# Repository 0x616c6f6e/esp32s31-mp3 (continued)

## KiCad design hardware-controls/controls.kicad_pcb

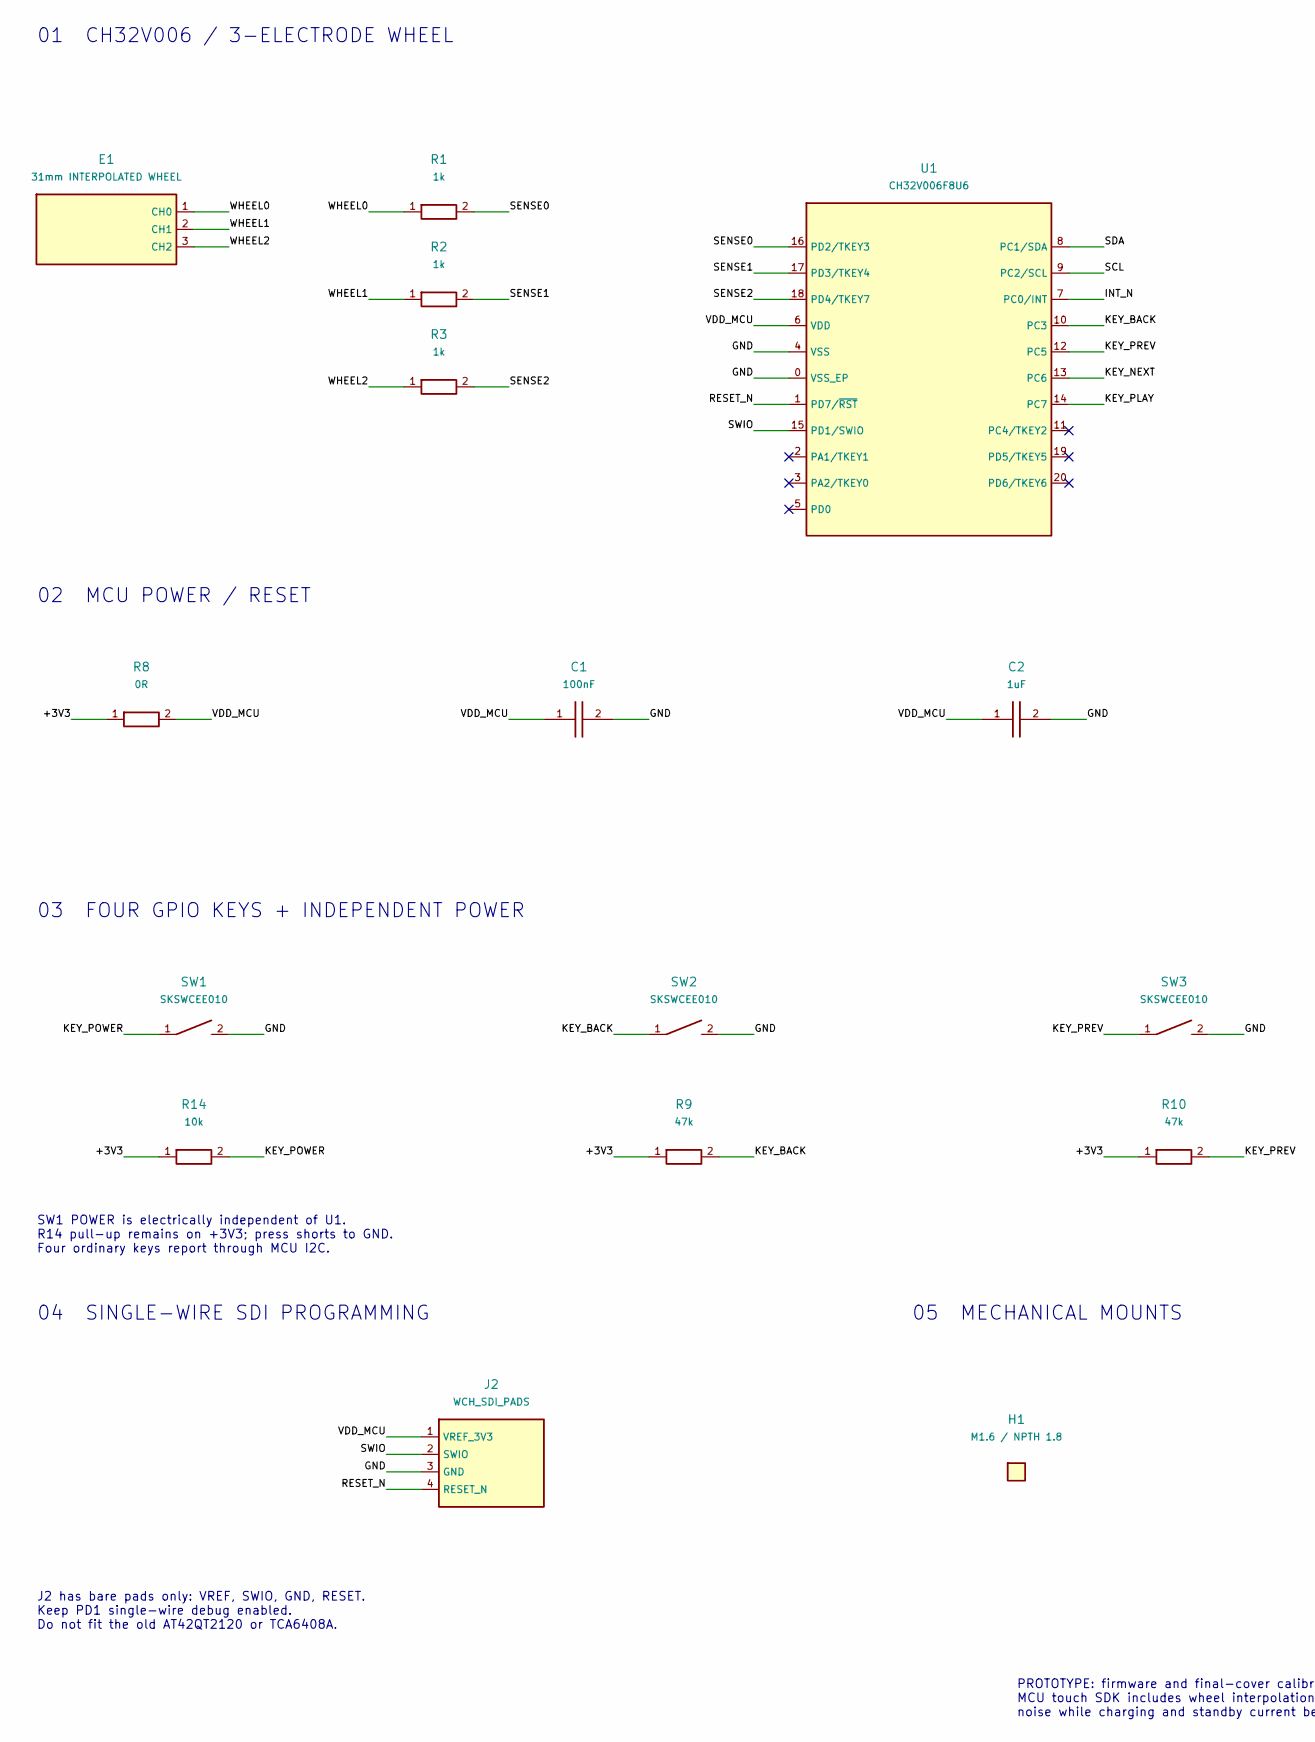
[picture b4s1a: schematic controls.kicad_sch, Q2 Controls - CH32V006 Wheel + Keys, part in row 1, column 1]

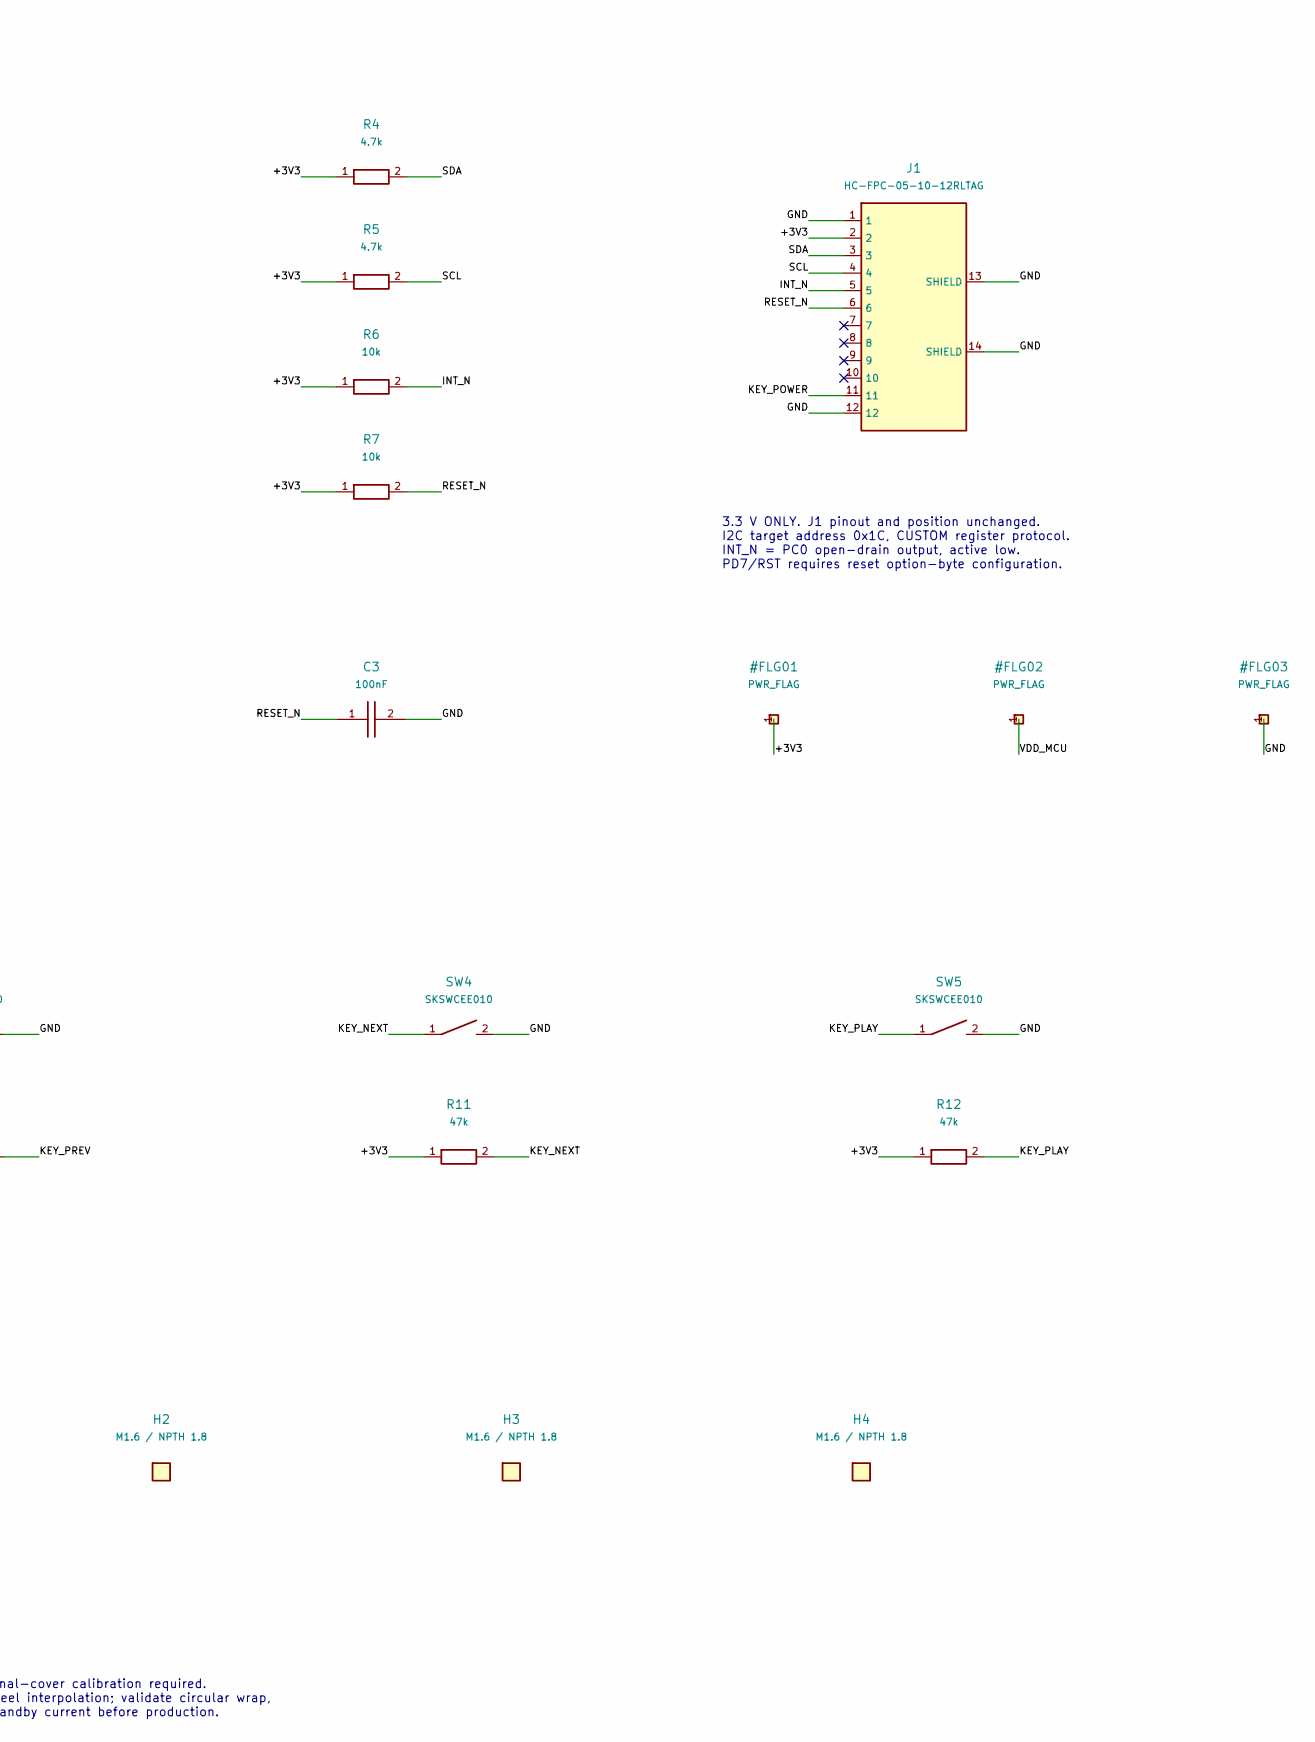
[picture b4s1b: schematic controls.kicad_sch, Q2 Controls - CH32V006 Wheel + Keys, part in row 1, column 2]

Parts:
C1, C3: 100nF; C0402
C2: 1uF; C0402
E1: 31mm INTERPOLATED WHEEL; Wheel_D31
H1, H2, H3, H4: M1.6 / NPTH 1.8; Mount_1.8
J1: HC-FPC-05-10-12RLTAG; HCTL_FPC12
J2: WCH_SDI_PADS; SDI_4_Pads
R1, R2, R3: 1k; R0402
R4, R5: 4.7k; R0402
R6, R7, R14: 10k; R0402
R8: 0R; R0402
R9, R10, R11, R12: 47k; R0402
SW1, SW2, SW3, SW4, SW5: SKSWCEE010; SKSW_3x2
U1: CH32V006F8U6; CH32V006_QFN20

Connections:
/+3V3: J1.2, R4.1, R5.1, R6.1, R7.1, R8.1, R9.1, R10.1, R11.1, R12.1, R14.1
/GND: C1.2, C2.2, C3.2, J1.1, J1.12, J1.13 (SHIELD), J1.14 (SHIELD), J2.3 (GND), SW1.2, SW2.2, SW3.2, SW4.2, SW5.2, U1.0 (VSS_EP), U1.4 (VSS)
/INT_N: J1.5, R6.2, U1.7 (PC0/INT)
/KEY_BACK: R9.2, SW2.1, U1.10 (PC3)
/KEY_NEXT: R11.2, SW4.1, U1.13 (PC6)
/KEY_PLAY: R12.2, SW5.1, U1.14 (PC7)
/KEY_POWER: J1.11, R14.2, SW1.1
/KEY_PREV: R10.2, SW3.1, U1.12 (PC5)
/RESET_N: C3.1, J1.6, J2.4 (RESET_N), R7.2, U1.1 (PD7/~RST)
/SCL: J1.4, R5.2, U1.9 (PC2/SCL)
/SDA: J1.3, R4.2, U1.8 (PC1/SDA)
/SENSE0: R1.2, U1.16 (PD2/TKEY3)
/SENSE1: R2.2, U1.17 (PD3/TKEY4)
/SENSE2: R3.2, U1.18 (PD4/TKEY7)
/SWIO: J2.2 (SWIO), U1.15 (PD1/SWIO)
/VDD_MCU: C1.1, C2.1, J2.1 (VREF_3V3), R8.2, U1.6 (VDD)
/WHEEL0: E1.1 (CH0), R1.1
/WHEEL1: E1.2 (CH1), R2.1
/WHEEL2: E1.3 (CH2), R3.1

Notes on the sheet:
01 CH32V006 / 3-ELECTRODE WHEEL
02 MCU POWER / RESET
03 FOUR GPIO KEYS + INDEPENDENT POWER
04 SINGLE-WIRE SDI PROGRAMMING
05 MECHANICAL MOUNTS
3.3 V ONLY. J1 pinout and position unchanged. I2C target address 0x1C, CUSTOM register protocol. INT_N = PC0 open-drain output, active low. PD7/RST requires reset option-byte configuration.
SW1 POWER is electrically independent of U1. R14 pull-up remains on +3V3; press shorts to GND. Four ordinary keys report through MCU I2C.
J2 has bare pads only: VREF, SWIO, GND, RESET. Keep PD1 single-wire debug enabled. Do not fit the old AT42QT2120 or TCA6408A.
PROTOTYPE: firmware and final-cover calibration required. MCU touch SDK includes wheel interpolation; validate circular wrap, noise while charging and standby current before production.

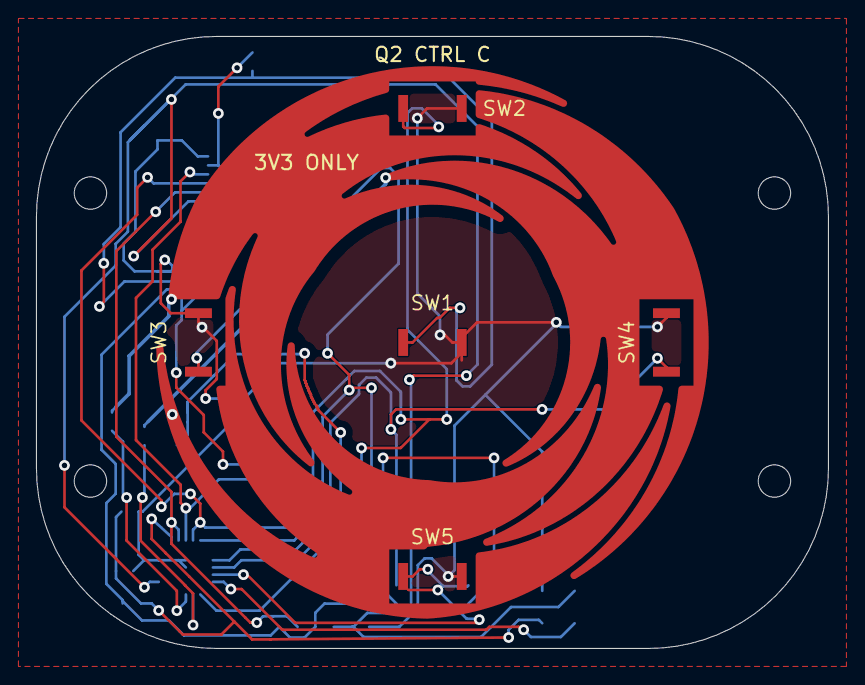
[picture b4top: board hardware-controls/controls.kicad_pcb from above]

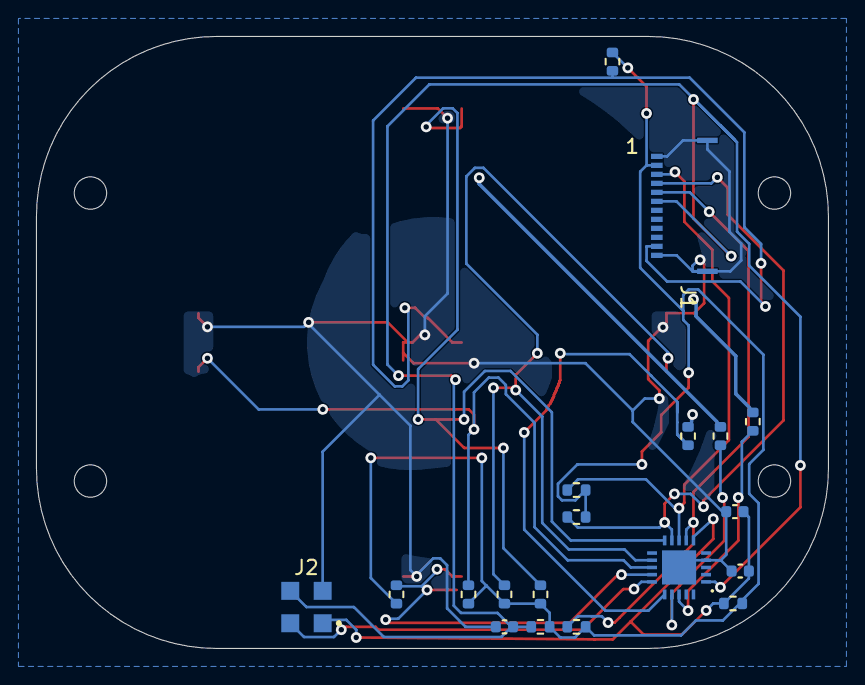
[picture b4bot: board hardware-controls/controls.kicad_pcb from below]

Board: 2 copper layers, 44.0 x 34.0 mm, 29 parts (19 on the bottom side), 19 nets.

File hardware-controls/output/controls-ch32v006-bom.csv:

"Designator","Value","Footprint","Quantity"
"C1,C3","100nF","Controls:C0402","2"
"C2","1uF","Controls:C0402","1"
"J1","HC-FPC-05-10-12RLTAG","Controls:HCTL_FPC12","1"
"R1-R3","1k","Controls:R0402","3"
"R4,R5","4.7k","Controls:R0402","2"
"R6,R7,R14","10k","Controls:R0402","3"
"R8","0R","Controls:R0402","1"
"R9-R12","47k","Controls:R0402","4"
"SW1-SW5","SKSWCEE010","Controls:SKSW_3x2","5"
"U1","CH32V006F8U6","Controls:CH32V006_QFN20","1"

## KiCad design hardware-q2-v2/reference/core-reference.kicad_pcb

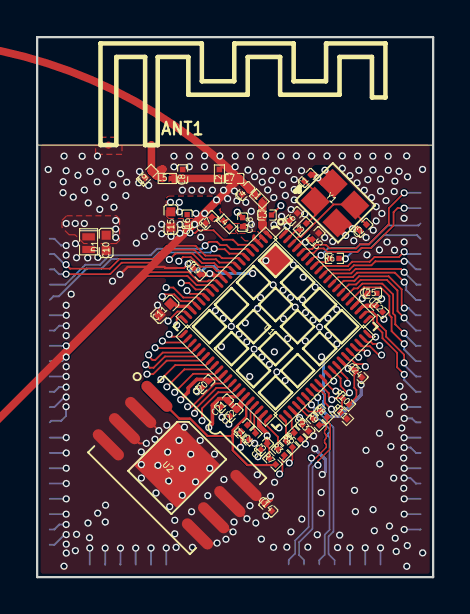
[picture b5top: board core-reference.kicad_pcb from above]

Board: 4 copper layers, 22.0 x 30.0 mm, 47 parts (1 on the bottom side), 85 nets.

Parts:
ANT1: ESP-ANT-2G-MIFA-G2-L15P8W5P6-V1P1
C1, C2, C3, C4, C5, C6, C7, C8, C12, C13, C14, C16, C17, C18, C19, C20, C21, C22, C23, C24, C25: C0201
C9: DFN0603_A
C10, C11, C15: C0402
D1: SOD882
L1, L2, L3, L4, L5: L0201
R1, R2, R3, R4, R5, R6, R7, R8, R9, R10, R11: R0201
U1: QFN80_0P35_8_E6P5_A
U2: WSON8_1P27_8X6_E4P3X3P4
U3: QFN94_0P85_22P6X20P6_MINI
Y1: XTAL3225_2016

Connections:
ANT: C3.1, L1.2, U1.1
EN: U1.4, U3.5
GND: ANT1.2, C1.2, C2.2, C3.2, C4.2, C5.2, C6.2, C8.2, C9.2, C10.2, C11.2, C12.2, C13.2, C14.2, C15.2, C16.2, C17.2, C18.2, C19.2, C20.2, C21.2, C22.2, C23.2, C24.2, C25.2, D1.1, L2.2, R11.2, U1.81, U2.4, U2.9, U3.1, U3.2, U3.26, U3.47, U3.48, U3.72, U3.73, U3.74, U3.75, U3.76, U3.77, U3.78, U3.79, U3.80, U3.81, U3.82, U3.83, U3.84, U3.85, U3.86, U3.87, U3.88, U3.89, U3.90, U3.92, U3.93, U3.94, U3.95, U3.96, U3.97, U3.98, U3.99, Y1.2, Y1.4
IO0: U1.5, U3.8
IO1: U1.6, U3.9
IO2: U1.7, U3.6
IO3: U1.8, U3.7
IO4: U1.9, U3.10
IO5: U1.10, U3.11
IO6: U1.12, U3.12
IO7: U1.13, U3.13
IO8: U1.14, U3.14
IO9: U1.15, U3.15
IO10: U1.16, U3.16
IO11: U1.17, U3.17
IO12: U1.19, U3.18
IO13: U1.20, U3.19
IO14: U1.21, U3.20
IO15: U1.22, U3.21
IO16: U1.23, U3.22
IO17: U1.24, U3.23
IO18: U1.25, U3.24
IO19: U1.26, U3.25
IO33: U1.46, U3.42
IO34: U1.47, U3.43
IO35: U1.48, U3.44
IO36: R10.1, R11.1, U1.49, U3.45
IO37: U1.50, U3.46
IO38: U1.51, U3.49
IO39: U1.52, U3.50
IO40: U1.53, U3.51
IO42: U1.55, U3.52
IO43: U1.56, U3.53
IO44: U1.57, U3.54
IO45: U1.58, U3.55
IO46: U1.59, U3.56
IO47: U1.60, U3.57
IO48: U1.61, U3.58
IO49: U1.62, U3.59
IO50: U1.65, U3.60
IO51: U1.66, U3.61
IO52: U1.67, U3.62
IO53: U1.68, U3.63
IO54: U1.69, U3.64
IO55: U1.70, U3.65
IO56: U1.71, U3.66
IO57: U1.72, U3.67
IO60: U1.75, U3.70
IO61: U1.76, U3.71
N20805107: C18.1, L4.2, U1.2, U1.3
N20805446: R6.1, U1.73
N20805524: L3.1, U1.79
N20805709: R4.1, U1.41
N20805715: R5.1, U1.42
N20805727: R3.1, U1.40
N20805734: R2.1, U1.38
N20805749: R1.1, U1.37
N20805764: R8.1, U1.45
N20805766: R9.1, U1.44
RF: C4.1, C7.2, L1.1
RF1: C7.1, C8.1, L2.1, L5.2
RF_ANT: ANT1.1, C9.1, L5.1
RX0: U1.74, U3.69
SD_CLK: U1.32, U3.31
SD_CMD: U1.33, U3.32
SD_D0: U1.27, U3.27
SD_D1: U1.28, U3.28
SD_D2: U1.29, U3.29
SD_D3: U1.31, U3.30
SPICLK: R4.2, U2.6
SPICS: R7.2, U1.36, U2.1
SPID: R5.2, U2.5
SPIHD: R3.2, U2.7
SPIQ: R1.2, U2.2
SPIWP: R2.2, U2.3
TX0: R6.2, U3.68
USB_DM: R8.2, U3.41
USB_DP: R9.2, U3.40
VDD33: C5.1, C6.1, C10.1, C15.1, C16.1, C17.1, C19.1, C23.1, C24.1, C25.1, D1.2, L4.1, R10.2, U1.11, U1.43, U1.54, U1.64, U1.77, U1.80, U3.3, U3.4
VDD_LDO_1P8: C20.1, C21.1, C22.1, U1.30, U1.34, U1.35
VDD_SPI: C13.1, C14.1, R7.1, U1.39, U2.8
VREF_ADC: C12.1, U1.63
VREF_TOUCH: C11.1, U1.18
XTAL_N: C2.1, U1.78, Y1.3
XTAL_P: C1.1, L3.2, Y1.1

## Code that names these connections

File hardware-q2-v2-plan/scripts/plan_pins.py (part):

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def fixed(pin,group,signal,target,reset,notes=''):
 r=rows[pin];assert r['group']=='未分配';r.update(group=group,signal=signal,target=target,reset_requirement=reset,notes=notes,direction='专用')

# LP GPIOs remain available for wake inputs; GPIO0 here is not an ESP32-S31 boot strap.
for g,s,old,target in [(0,'KEY_POWER_SENSE_N','ESP_IO42','FPC1.11 / U6.1，经3.3V隔离检测'),(1,'CTRL_INT_N','ESP_IO43','FPC1.5'),(2,'RTC_INT_N','ESP_IO34','U1.6'),(3,'IMU_INT1','ESP_IO1','U15.4'),(4,'BAT_ALERT_N','ESP_IO35','U14.1'),(5,'CHG_INT_N','BQ25895_INT','U3.7')]:
 assign(g,'唤醒/中断',s,old,'输入',target,'输入；上拉仅接3.3V；GPIO3极性由IMU配置','LP GPIO；唤醒需要固件配置。KEY必须隔离GEK供电域；不得原样直连。' if g==0 else 'LP GPIO；可按需要配置唤醒，保持供电时才有效。')
assign(6,'系统LP I2C','SYS_I2C_SCL','BQ25895_I2C_CLK','开漏双向','U3.5 U14.3 U1.2 U11.2 FPC1.4','外部上拉3.3V','LP I2C，F2；100kHz起步；不是I2C_NUM_2')
assign(7,'系统LP I2C','SYS_I2C_SDA','BQ25895_I2C_SDA','开漏双向','U3.6 U14.2 U1.3 U11.3 FPC1.3','外部上拉3.3V','LP I2C，F2；LP核访问须与主核通过命令/共享内存协调')
for g,s,old,di,t,reset,note in [
 (9,'POWER_OFF_REQ','GEK100_RST','输出','U6.3，经断电防反灌电路','外部下拉；上电低','新增软件关机请求；高有效，需保证掉电后复位脉冲时长'),
 (10,'CTRL_RESET_N','ESP_IO44','开漏输出','FPC1.6','释放，由小板RC上拉','CH32V006 PD7配置硬件复位后才生效'),
 (11,'USB_PATH_SEL','ESP_IO33','输出','U17.2','外部电阻固定默认路径','避开GPIO33复位USB功能；0/1对应哪路须核对U17真值表'),
 (12,'MOTOR_EN','ESP_IO40','输出','U11.5','外部下拉；默认关闭','保留现有R44下拉；PWM/触发使用需按马达驱动配置'),
 (13,'CHG_OTG_EN','BQ25895_OTG_EN','输出','U3.8','外部下拉；默认关闭','保留R12下拉；不得上电即打开OTG'),
 (19,'SD_CARD_DETECT_N','ESP_IO19','输入','CARD2.CD','新增/核对3.3V上拉','检测触点极性以实物卡座导通确认')]:
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 assign(g,'SDMMC',s,old,'输出' if g==24 else '双向',t,'CMD/D0-D3上拉3.3V；CLK不随意加上拉','原生SDIO F0；本板卡接口先用3.3V，不直接改1.8V模式')
for g,s,old,t in [(26,'FLASH_CS_N','ESP_FLASH_CS','U10.1'),(27,'FLASH_D1','ESP_FLASH_DO','U10.2'),(28,'FLASH_D2','ESP_FLASH_WP','U10.3'),(30,'FLASH_D3','ESP_FLASH_HOLD','U10.7'),(31,'FLASH_CLK','ESP_FLASH_CLK','U10.6'),(32,'FLASH_D0','ESP_FLASH_DI','U10.5')]:
 assign(g,'启动Flash',s,old,'输出' if g in [26,31] else '双向',t,'按启动Flash参考电路','固定MSPI引脚；不分给应用GPIO；U10容量待选，建议与原模组16MB目标一致')
fixed(44,'USB HS','USB_HS_DP','U17.7','专用差分','旧网ESP_USB_DP；不是GPIO44')
fixed(45,'USB HS','USB_HS_DM','U17.6','专用差分','旧网ESP_USB_DN；不是GPIO45')
assign(33,'调试预留','USB_DEBUG_DM','','专用差分','新增调试焊盘/连接器','保留USB Serial/JTAG功能','不再接USB切换SEL；与HS USB不是同一对线，不可并接')
assign(34,'调试预留','USB_DEBUG_DP','','专用差分','新增调试焊盘/连接器','保留USB Serial/JTAG功能','不再接RTC中断；量产无调试连接器时可不装引出件')
for g,s,old,t in [(35,'DAC_I2S_DOUT','DAC_I2S_SDIN','U8.2'),(38,'DAC_I2S_LRCK','DAC_I2S_LRCK','U8.5'),(39,'DAC_RESET_N','DAC_RST#','U8.12'),(40,'DAC_I2S_BCLK','DAC_I2S_SCLK','U8.9')]:
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assign(59,'下载UART0','UART0_RX','CH343P_UART_TX','输入','U12.4 TXD','UART0输入','ESP RX接CH343 TX')
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 assign(g,'启动配置',s,old,'启动采样','启动上拉/下载电路',reset,note)
fixed(4,'复位','CHIP_PU','RC及CH343下载控制电路','10k上拉/RC按参考设计','旧网ESP32S31_EN；必须核对自动下载握手，不能误当普通GPIO')
rows[4]['old_net']='ESP32S31_EN';rows[44]['old_net']='ESP_USB_DP';rows[45]['old_net']='ESP_USB_DN'
fixed(1,'射频','ANT','RF匹配/天线','按RF参考设计','专用射频端口')
for pin in [2,3,11,43,54,64,77,80]:
 if rows[pin]['group']=='未分配':fixed(pin,'电源','3V3_'+names[pin-1],'3.3V域，局部滤波/去耦','按每个电源脚放去耦','VDDA模拟电源滤波不可省略')
for pin in [30,34]:fixed(pin,'电源',names[pin-1],'VDD_LDO_1P8，按参考电路','1.8V PSRAM供电','不是3.3V输入')
fixed(35,'电源','VDD_LDO_1P8','PSRAM 1.8V供电和去耦','芯片电源输出','不能接外部3.3V')
fixed(39,'电源','VDD_SPI','外接Flash供电/去耦','按3.3V Flash参考电路','结合GPIO36配置；不是任意与外部电源并接')
fixed(78,'晶振','XTAL_N','40MHz晶振/匹配','专用时钟','按乐鑫参考设计，不能随意加长/过孔')
fixed(79,'晶振','XTAL_P','40MHz晶振/匹配','专用时钟','需要参考设计指定的串联电感/负载网络')
fixed(81,'地','GND_EP','连续GND/散热过孔','可靠接地','封装中央裸露焊盘，不是GPIO81')
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assert all(r['signal'] for r in plan)
assert len({r['signal'] for r in plan})==81
assert all(rows[gpio_to_pin[g]]['group']=='启动配置' for g in [36,37,60,61])
assert [rows[gpio_to_pin[g]]['signal'] for g in [52,53,54,55,56,57]]==['LCD_CS_N','LCD_CLK','LCD_D0','LCD_D1','LCD_D3','LCD_D2']
used_nets={a['old_net'] for a in plan if a['old_net']}
source_path=R/'hardware-q2/ProPrj_esp32s31-mp4_2026-09-22.kicad_pcb'
source=parse(source_path.read_text(encoding='utf8'));old_u9=next(f for f in children(source,'footprint') if prop(f,'Reference')[2]=='U9')
old_nets={get(a,'net')[1] for a in children(old_u9,'pad') if get(a,'net') and get(a,'net')[1] not in ['', 'GND','VCC_3V3']}
excluded={'ESP_IO4':'旧板无外围连接，改作电池告警','ESP_IO5':'旧板无外围连接，改作充电中断','ESP_IO45':'旧TFT背光控制删除；新GPIO45用于AMOLED使能'}
assert old_nets-used_nets==set(excluded),(old_nets-used_nets)
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audit['source_mainboard_sha256']=hashlib.sha256(source_path.read_bytes()).hexdigest()
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for a in plan:
 if a['gpio'] is not None and a['group'] not in ['启动Flash','启动配置','调试预留','空闲GPIO']:
  header.extend([f"/* QFN pin {a['pin']}; {a['target']} */",f"#define Q2_{a['signal']}_GPIO {a['gpio']}"])
header+=['/* LP I2C is NOT a third HP I2C controller. Initialize through LP APIs. */','#define Q2_SYS_I2C_INITIAL_HZ 100000','#define Q2_AUDIO_I2C_HP_PORT 0','#define Q2_TP_I2C_HP_PORT 1','#define Q2_LCD_SPI_INITIAL_HZ 20000000','/* Native USB HS uses dedicated QFN pins 44/45, never GPIO44/45. */']
(P/'q2_v2_pin_plan.h').write_text('\n'.join(header)+'\n',encoding='utf8')
table=['# 第二版引脚分配完整表','', '候选方案：ESP32-S31NRV16；KiCad −90°。GPIO编号与QFN物理脚号分别列出。尚未写入原理图/PCB。','', '| 物理脚 | 芯片脚名 | GPIO | 功能分组 | 建议网络名 | 旧网络 | 目标 |','|---:|---|---:|---|---|---|---|']
for a in plan:table.append('| '+' | '.join(str(a[k]) if a[k] is not None else '—' for k in ['pin','pin_name','gpio','group','signal','old_net','target'])+' |')
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
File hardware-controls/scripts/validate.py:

"""Read-only native design audit; consumes refreshed KiCad and FreeCAD reports."""
from pathlib import Path
import hashlib,json,math,zipfile,subprocess
import pcbnew as p
P=Path(__file__).resolve().parents[1];ROOT=P.parent
sha=lambda f:hashlib.sha256(f.read_bytes()).hexdigest()
b=p.LoadBoard(str(P/'controls.kicad_pcb'))
data=json.loads((P/'output/design.json').read_text(encoding='utf8'))
assert data['connector_pinout']==['GND','+3V3','SDA','SCL','INT_N','RESET_N',None,None,None,None,'KEY_POWER','GND']
spec={c['ref']:c for c in data['components']};fps={f.GetReference():f for f in b.GetFootprints()}
assert set(fps)==set(spec) and len(fps)==42
for ref,f in fps.items():
 c=spec[ref];x,y,side,angle=c['pcb']
 assert f.GetPath().AsString()=='/'+data['root_uuid']+'/'+c['symbol_uuid'],ref
 assert f.GetValue()==c['value'] and f.GetFPIDAsString()=='Controls:'+c['footprint'],ref
 assert math.hypot(f.GetPosition().x/1e6-(44-x),f.GetPosition().y/1e6-y)<1e-5,ref
 assert f.IsFlipped()==(side=='B'),ref
 for pad in f.Pads():
  if pad.GetNumber() in c['nets']:assert pad.GetNetname()=='/'+c['nets'][pad.GetNumber()],(ref,pad.GetNumber())
assert b.GetCopperLayerCount()==2 and abs(b.GetDesignSettings().GetBoardThickness()/1e6-.8)<1e-6
assert sum(len(f.Models()) for f in fps.values())==26
# Interface audit: four digital keys terminate at U2, never at J1; POWER
# is independent of both ICs and pulled up to +3V3 by R14.
members={}
for ref,f in fps.items():
 for a in f.Pads():
  if a.GetNumber():members.setdefault(a.GetNetname(),set()).add((ref,a.GetNumber()))
assert members['/KEY_POWER']=={('SW1','1'),('J1','11'),('TP7','1'),('R14','2')}
assert fps['R14'].GetValue()=='10k'
assert {('R14','1'),('J1','2')} <= members['/+3V3']
assert ('SW1','2') in members['/GND']
assert {('U1','11'),('U2','13'),('J1','3'),('R4','2'),('TP3','1')}==members['/SDA']
assert {('U1','14'),('U2','12'),('J1','4'),('R5','2'),('TP4','1')}==members['/SCL']
for i,name in enumerate(['BACK','PREV','NEXT','PLAY']):
 assert members['/KEY_'+name]=={('SW'+str(i+2),'1'),('U2',str(i+2)),('R'+str(i+9),'2'),('TP'+str(i+8),'1')}
for n in ['7','8','9','10']:
 pad=next(a for a in fps['J1'].Pads() if a.GetNumber()==n)
 assert pad.GetNetname().startswith('unconnected-') and len(members[pad.GetNetname()])==1
assert {('U1','15'),('U2','11'),('J1','5'),('R6','2'),('TP5','1')}==members['/INT_N']
assert {('U1','12'),('U2','1'),('J1','6'),('R7','2'),('TP6','1')}==members['/RESET_N']
assert {('U2',str(n)) for n in [7,8,9,10]}|{('R13','1')}==members['/UNUSED_INPUTS']
electrode=[]
for pad in fps['E1'].Pads():
 assert pad.IsOnLayer(p.F_Cu) and not any(pad.IsOnLayer(l) for l in [p.B_Cu,p.F_Mask,p.F_Paste])
 poly=pad.GetEffectivePolygon(p.F_Cu);assert poly.OutlineCount()==1
 line=poly.COutline(0);pp=[(line.CPoint(i).x/1e6,line.CPoint(i).y/1e6) for i in range(line.PointCount())]
 area=abs(sum(a[0]*z[1]-z[0]*a[1] for a,z in zip(pp,pp[1:]+pp[:1])))/2
 electrode.append({'pin':pad.GetNumber(),'net':pad.GetNetname(),'connected_islands':1,'copper_area_mm2':round(area,4)})
drc=json.loads((P/'output/drc.json').read_text());erc=json.loads((P/'output/erc.json').read_text())
assert not drc['violations'] and not drc['unconnected_items'] and not drc['schematic_parity']
assert not [v for s in erc['sheets'] for v in s['violations']]
fit=json.loads((P/'mechanical/fit-check.json').read_text(encoding='utf8'))
assert fit['pass'] and fit['controls_pcb_sha256']==sha(P/'controls.kicad_pcb'),'Refresh mechanical report'
plan=json.loads((P/'mechanical/interconnect-plan.json').read_text())
assert fit['source_sha256']['mainboard']==plan['mainboard_sha256']==sha(ROOT/plan['mainboard'])
assert fit['source_sha256']['enclosure']==sha(ROOT/'mechanical/enclosure-q2-f/ESP32S31_MP3_Q2_F.FCStd')
assert fit['interconnect']['nominal_route_pass'] and fit['interconnect']['pin_mapping']=={str(i):i for i in range(1,13)}
host=p.LoadBoard(str(ROOT/plan['mainboard']));hc=host.FindFootprintByReference('FPC1')
hostpads={a.GetNumber():a for a in hc.Pads()};controlpads={a.GetNumber():a for a in fps['J1'].Pads()}
expected=['GND','VCC_3V3','BQ25895_I2C_SDA','BQ25895_I2C_CLK','ESP_IO43','ESP_IO44','','','','','ESP_IO42','GND']
for i,name in enumerate(expected,1):
 assert hostpads[str(i)].GetNetname()==name,(i,name)
 assert abs(hostpads[str(i)].GetPosition().y/1e6-65.647-(controlpads[str(i)].GetPosition().y/1e6+42.3))<1e-5,i
assert fps['J1'].GetValue()=='HC-FPC-05-10-12RLTAG'
assert all(controlpads[n].GetNetname()=='/GND' for n in ['13','14'])
subprocess.run(['git','diff','--quiet','HEAD','--','hardware-q2-placement/hardware.kicad_pcb','mechanical/enclosure-q2-f/ESP32S31_MP3_Q2_F.FCStd'],cwd=ROOT,check=True)
tracks=[t for t in b.GetTracks() if not isinstance(t,p.PCB_VIA)];vias=[t for t in b.GetTracks() if isinstance(t,p.PCB_VIA)]
report={'revision':'B','i2c_addresses':{'wheel':'0x1C','keys':'0x20'},'four_keys_i2c_only_at_connector':True,'power_independent_active_low':True,'power_pullup_ohm':10000,'power_pullup_rail':'+3V3','shared_open_drain_interrupt':True,'status':'ROUTED_STANDALONE_PROTOTYPE_REQUIRES_PHYSICAL_VALIDATION','pcb_sha256':sha(P/'controls.kicad_pcb'),'schematic_sha256':sha(P/'controls.kicad_sch'),'project_sha256':sha(P/'controls.kicad_pro'),'step_sha256':sha(P/'output/controls-populated.step'),'footprints':42,'physical_components':26,'front_components':5,'back_components':21,'schematic_links_verified':42,'copper_layers':2,'board_mm':[44,34,.8],'track_segments':len(tracks),'vias':len(vias),'track_widths_mm':sorted({round(t.GetWidth()/1e6,4) for t in tracks}),'via_drills_mm':sorted({round(t.GetDrill()/1e6,4) for t in vias}),'drc_violations':0,'unconnected_items':0,'schematic_parity_issues':0,'erc_violations':0,'electrodes':electrode,'nominal_mechanical_fit_pass':True,'mainboard_connected':False,'mainboard_and_source_enclosure_unchanged':True,'production_release':False}
report['fabrication_files_sha256']={f.name:sha(f) for f in sorted((P/'fabrication').iterdir()) if f.is_file()}
report['connector_pinout']=data['connector_pinout']
report['mainboard_source']=plan['mainboard']
report['interconnect']={'cable':'12P / 0.5mm / 40mm / B opposite contacts / 0.3mm terminal','nominal_geometry_pass':True,'sample_validation_required':True,'mainboard_mounting_posts_pending':True,'mainboard_source_sha256':plan['mainboard_sha256']}
(P/'output/validation.json').write_text(json.dumps(report,ensure_ascii=False,indent=2)+'\n',encoding='utf8')
data['status']=report['status'];data['pcb_sha256']=report['pcb_sha256'];(P/'output/design.json').write_text(json.dumps(data,ensure_ascii=False,indent=2)+'\n',encoding='utf8')
with zipfile.ZipFile(P/'output/controls-B-prototype-gerbers.zip','w',zipfile.ZIP_DEFLATED) as z:
 for f in sorted((P/'fabrication').iterdir()):
  if f.is_file():z.write(f,f.name)
print('CONTROLS_VALIDATED',json.dumps(report,ensure_ascii=False))

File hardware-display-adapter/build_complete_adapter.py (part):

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component('J2','J_LCD','OK-23GF024-04',screen,(220,60),'OK23GF024',(53,62,0),desc='Top view: 1 upper left, 12 lower left, 13 lower right, 24 upper right; OSPTEK board photo')
for i,(n,out,xy) in enumerate([('CLK_IN','LCD_CLK',(57,59)),('CS_IN','LCD_CS',(57,57)),('D0_IN','LCD_D0',(57,63)),('D1_IN','LCD_D1',(57,61)),('D2_IN','LCD_D2',(57,67)),('D3_IN','LCD_D3',(57,65))],1):
    component('R'+str(i),'R','22R' if i==1 else '0R',{1:n,2:out},(50+((i-1)%3)*95,125+((i-1)//3)*17.78),'R0402',(*xy,0),desc='QSPI series damping; initial conservative low clock, tune on scope')
component('R7','R','0R',{1:'VCC_3V3',2:'LCD_VDD'},(50,174),'R0402',(56,69.3,0),desc='Factory reference feeds pin15 at3.3V; removable isolation link')
component('R8','R','0R',{1:'VCC_3V3',2:'TP_VDD'},(145,174),'R0402',(56,70.8,0),desc='Factory reference feeds pin16 at3.3V; removable isolation link')
component('R9','R','100k',{1:'VCI_EN',2:'GND'},(240,174),'R0402',(56,54,0),desc='Default PMIC disable until ESP_IO46 asserts enable')
component('R10','R','4.7k',{1:'VCC_3V3',2:'TP_SDA'},(50,202),'R0402',(61,64,90),True,'Optional pull-up; host already has R46')
component('R11','R','4.7k',{1:'VCC_3V3',2:'TP_SCL'},(145,202),'R0402',(63,64,90),True,'Optional pull-up; host already has R45')
for ref,val,net,sch,xy,foot in [('C1','100nF','VCC_3V3',(50,230),(53,69.5),'C0402'),('C2','10uF','VCC_3V3',(145,230),(51.5,69.3),'C0603'),('C3','100nF','LCD_VDD',(240,230),(59,69.3),'C0402'),('C4','100nF','TP_VDD',(335,230),(59,70.8),'C0402')]:
    if ref=='C4':xy=(62,70.5)
    component(ref,'C',val,{1:net,2:'GND'},sch,foot,(*xy,90),desc='X5R/X7R 10V; C2 maximum assembled height <=0.8mm')
component('TP1','TP','TE 3V3',{1:'LCD_TE'},(335,125),'TP',(56,55.5,0),desc='No host GPIO allocated; TE unused in initial firmware')
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(O/(name+'.kicad_sch')).write_text(sch,encoding='utf-8')
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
